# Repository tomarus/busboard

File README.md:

Eurorack Busboard
=================

A eurorack power bus board in Kicad.

Size 31.5 x 200mm.

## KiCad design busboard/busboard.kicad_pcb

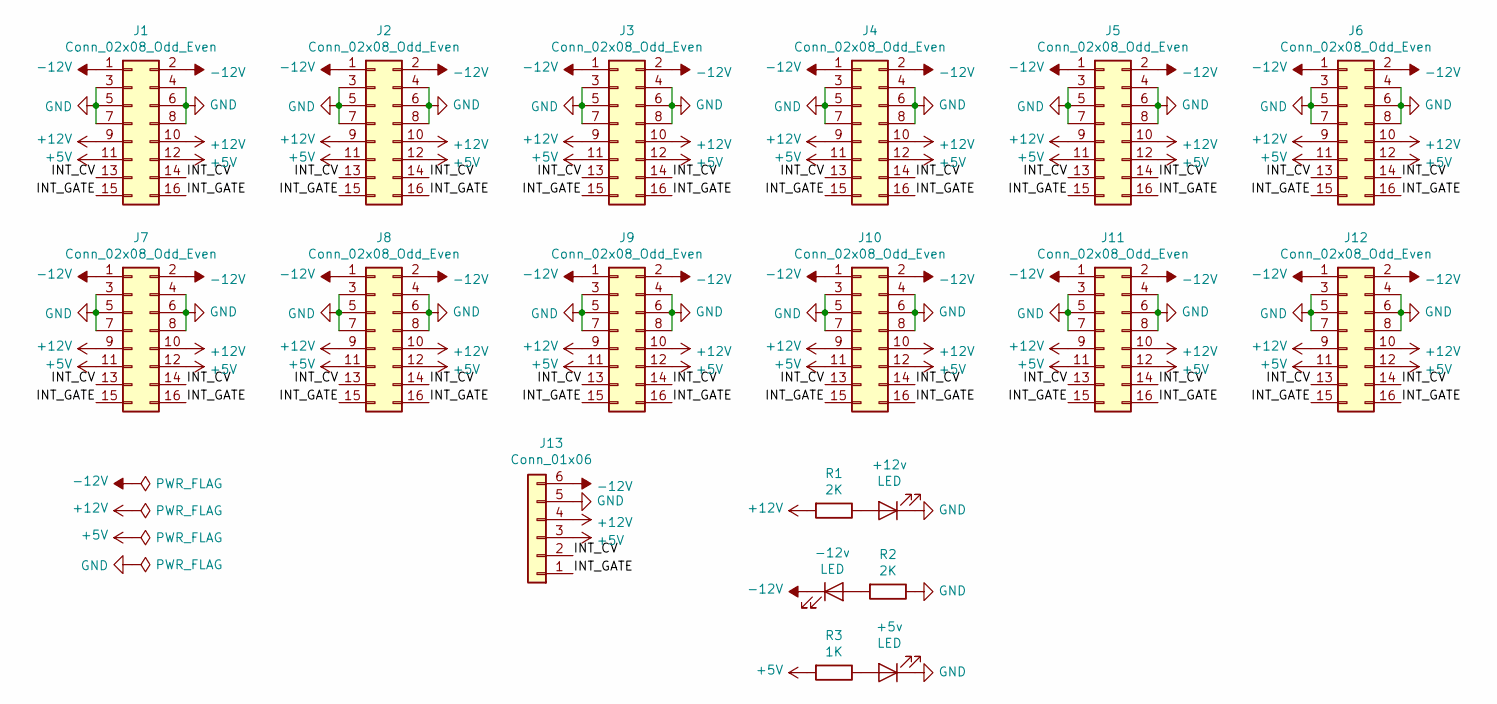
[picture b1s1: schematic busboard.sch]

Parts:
+5v, +12v: LED; LED_D3.0mm
-12v: LED; LED_D3.0mm
J1, J2, J3, J4, J5, J6, J7, J8, J9, J10, J11, J12: Conn_02x08_Odd_Even; IDC-Header_2x08_P2.54mm_Vertical_Eurorack
J13: Conn_01x06; TerminalBlock_RND_205-00236_1x06_P5.08mm_Horizontal
R1, R2: 2K; R_Axial_DIN0207_L6.3mm_D2.5mm_P7.62mm_Horizontal
R3: 1K; R_Axial_DIN0207_L6.3mm_D2.5mm_P7.62mm_Horizontal

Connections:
+5V: J1.11, J1.12, J2.11, J2.12, J3.11, J3.12, J4.11, J4.12, J5.11, J5.12, J6.11, J6.12, J7.11, J7.12, J8.11, J8.12, J9.11, J9.12, J10.11, J10.12, J11.11, J11.12, J12.11, J12.12, J13.3, R3.2
+12V: J1.9, J1.10, J2.9, J2.10, J3.9, J3.10, J4.9, J4.10, J5.9, J5.10, J6.9, J6.10, J7.9, J7.10, J8.9, J8.10, J9.9, J9.10, J10.9, J10.10, J11.9, J11.10, J12.9, J12.10, J13.4, R1.2
-12V: -12v.1 (K), J1.1, J1.2, J2.1, J2.2, J3.1, J3.2, J4.1, J4.2, J5.1, J5.2, J6.1, J6.2, J7.1, J7.2, J8.1, J8.2, J9.1, J9.2, J10.1, J10.2, J11.1, J11.2, J12.1, J12.2, J13.6
/INT_CV: J1.13, J1.14, J2.13, J2.14, J3.13, J3.14, J4.13, J4.14, J5.13, J5.14, J6.13, J6.14, J7.13, J7.14, J8.13, J8.14, J9.13, J9.14, J10.13, J10.14, J11.13, J11.14, J12.13, J12.14, J13.2
/INT_GATE: J1.15, J1.16, J2.15, J2.16, J3.15, J3.16, J4.15, J4.16, J5.15, J5.16, J6.15, J6.16, J7.15, J7.16, J8.15, J8.16, J9.15, J9.16, J10.15, J10.16, J11.15, J11.16, J12.15, J12.16, J13.1
GND: +5v.1 (K), +12v.1 (K), J1.3, J1.4, J1.5, J1.6, J1.7, J1.8, J2.3, J2.4, J2.5, J2.6, J2.7, J2.8, J3.3, J3.4, J3.5, J3.6, J3.7, J3.8, J4.3, J4.4, J4.5, J4.6, J4.7, J4.8, J5.3, J5.4, J5.5, J5.6, J5.7, J5.8, J6.3, J6.4, J6.5, J6.6, J6.7, J6.8, J7.3, J7.4, J7.5, J7.6, J7.7, J7.8, J8.3, J8.4, J8.5, J8.6, J8.7, J8.8, J9.3, J9.4, J9.5, J9.6, J9.7, J9.8, J10.3, J10.4, J10.5, J10.6, J10.7, J10.8, J11.3, J11.4, J11.5, J11.6, J11.7, J11.8, J12.3, J12.4, J12.5, J12.6, J12.7, J12.8, J13.5, R2.1
unnamed: +12v.2 (A), R1.1
unnamed: -12v.2 (A), R2.2
unnamed: +5v.2 (A), R3.1

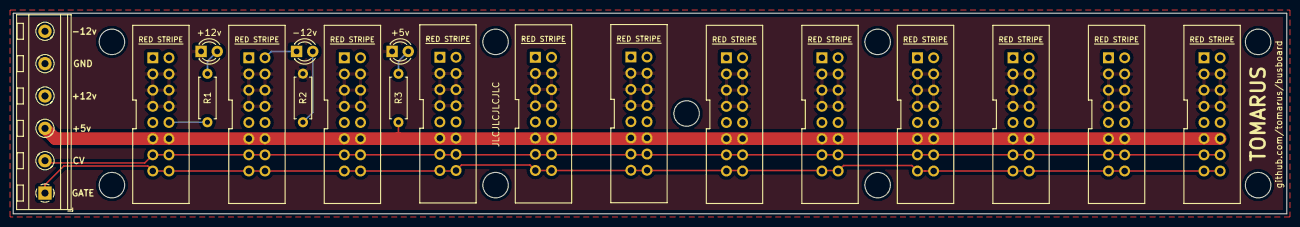
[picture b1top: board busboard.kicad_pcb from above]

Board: 2 copper layers, 200.0 x 31.5 mm, 19 parts (0 on the bottom side), 9 nets.

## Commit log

2019-10-18 Initial commit.
2019-10-24 Add picture.
